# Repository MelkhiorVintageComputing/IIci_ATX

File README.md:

An adapter to use an ATX power supply with a Mac IIci. Use at your own risk.

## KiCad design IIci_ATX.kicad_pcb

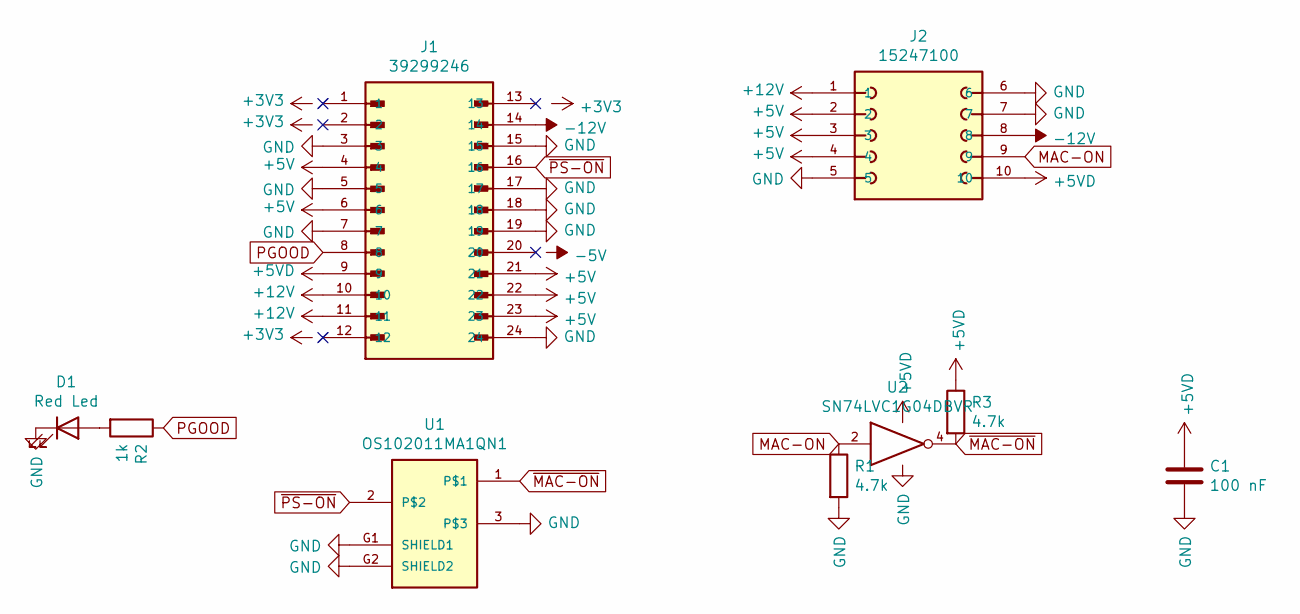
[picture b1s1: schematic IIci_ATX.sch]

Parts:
C1: 100 nF; C_0603_1608Metric; MPN CC0603KRX7R9BB104
D1: Red Led; LED_0805_2012Metric; MPN LTST-C170KRKT
J1: 39299246; MOLEX_39299246; PARTREV A1
J2: 15247100; MOLEX_15247100; PARTREV X5
R1, R3: 4.7k; R_0603_1608Metric; MPN 0603WAF4701T5E
R2: 1k; R_0603_1608Metric; MPN 0603WAF1001T5E
U1: OS102011MA1QN1; MPN OS102011MA1QN1
U2: SN74LVC1G04DBVR; SOT-23-5; MPN SN74LVC1G04DBVR

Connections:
+5V: J1.4, J1.6, J1.21, J1.22, J1.23, J2.2, J2.3, J2.4
+5VD: C1.2, J1.9, J2.10, R3.1, U2.5 (VCC)
+12V: J1.10, J1.11, J2.1
-12V: J1.14, J2.8
GND: C1.1, D1.1 (K), J1.3, J1.5, J1.7, J1.15, J1.17, J1.18, J1.19, J1.24, J2.5, J2.6, J2.7, R1.2, U1.3, U1.G1 (SHIELD1), U1.G2 (SHIELD2), U2.3 (GND)
MAC-ON: J2.9, R1.1, U2.2
unnamed: D1.2 (A), R2.2
PGOOD: J1.8, R2.1
~MAC-ON: R3.2, U1.1, U2.4
~PS-ON: J1.16, U1.2

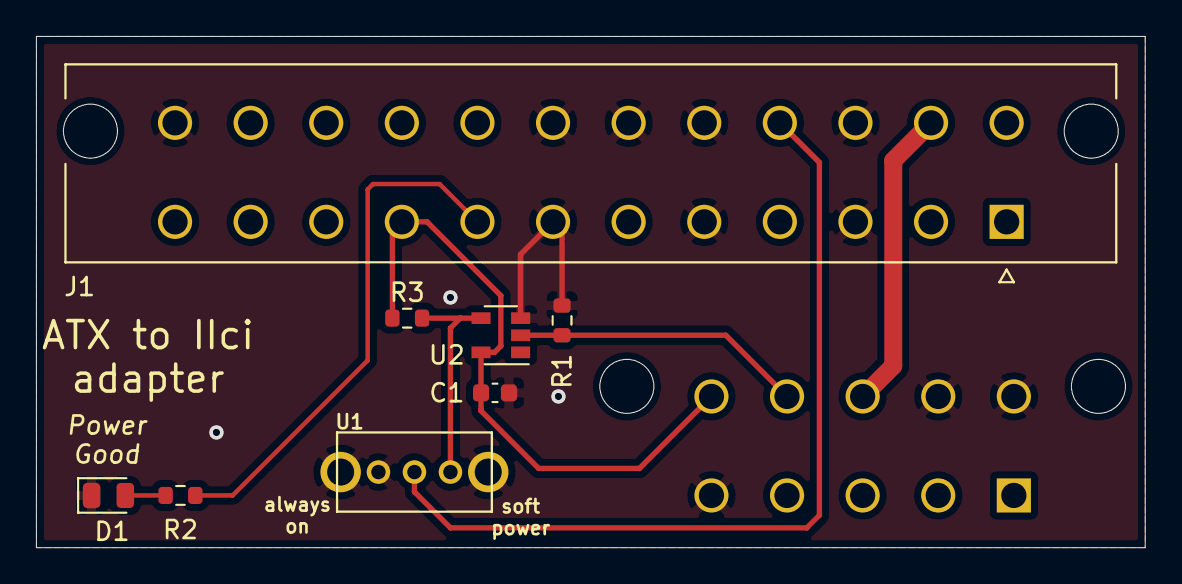
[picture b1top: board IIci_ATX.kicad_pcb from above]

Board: 4 copper layers, 61.6 x 28.4 mm, 9 parts (1 on the bottom side), 10 nets.

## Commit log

2023-02-28 initial import
2023-10-05 license
